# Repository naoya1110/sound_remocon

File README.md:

# sound_remocon

このリポジトリは、サウンドリモコンの開発データ（KiCadファイル等）をまとめたものです。

## ディレクトリ構成

- **v2/**  
  バージョン2
  - **kicad/**  
    v2用のKiCadプロジェクトファイル
    - `sound_remocon_v2/`：v2用KiCadプロジェクト・Gerberファイル
    - `plot_v2_20250704/`：v2 PCB製造用Gerberファイル
  - **ltspice/**  
    LTspiceシミュレーションファイル
    - `mixer_circuit_simulation.asc`：ミキサー回路シミュレーション
  - **pico_codes/**  
    - `pico_codes\sound_remocon_v2\sound_remocon_v2.ino` ラズパイPico用ファームウェア・コード

- **v1/**  
  バージョン1
  - **kicad/**  
    KiCadプロジェクトファイル、ネットリスト、シンボルライブラリ、フットプリント、Gerberファイルなど。

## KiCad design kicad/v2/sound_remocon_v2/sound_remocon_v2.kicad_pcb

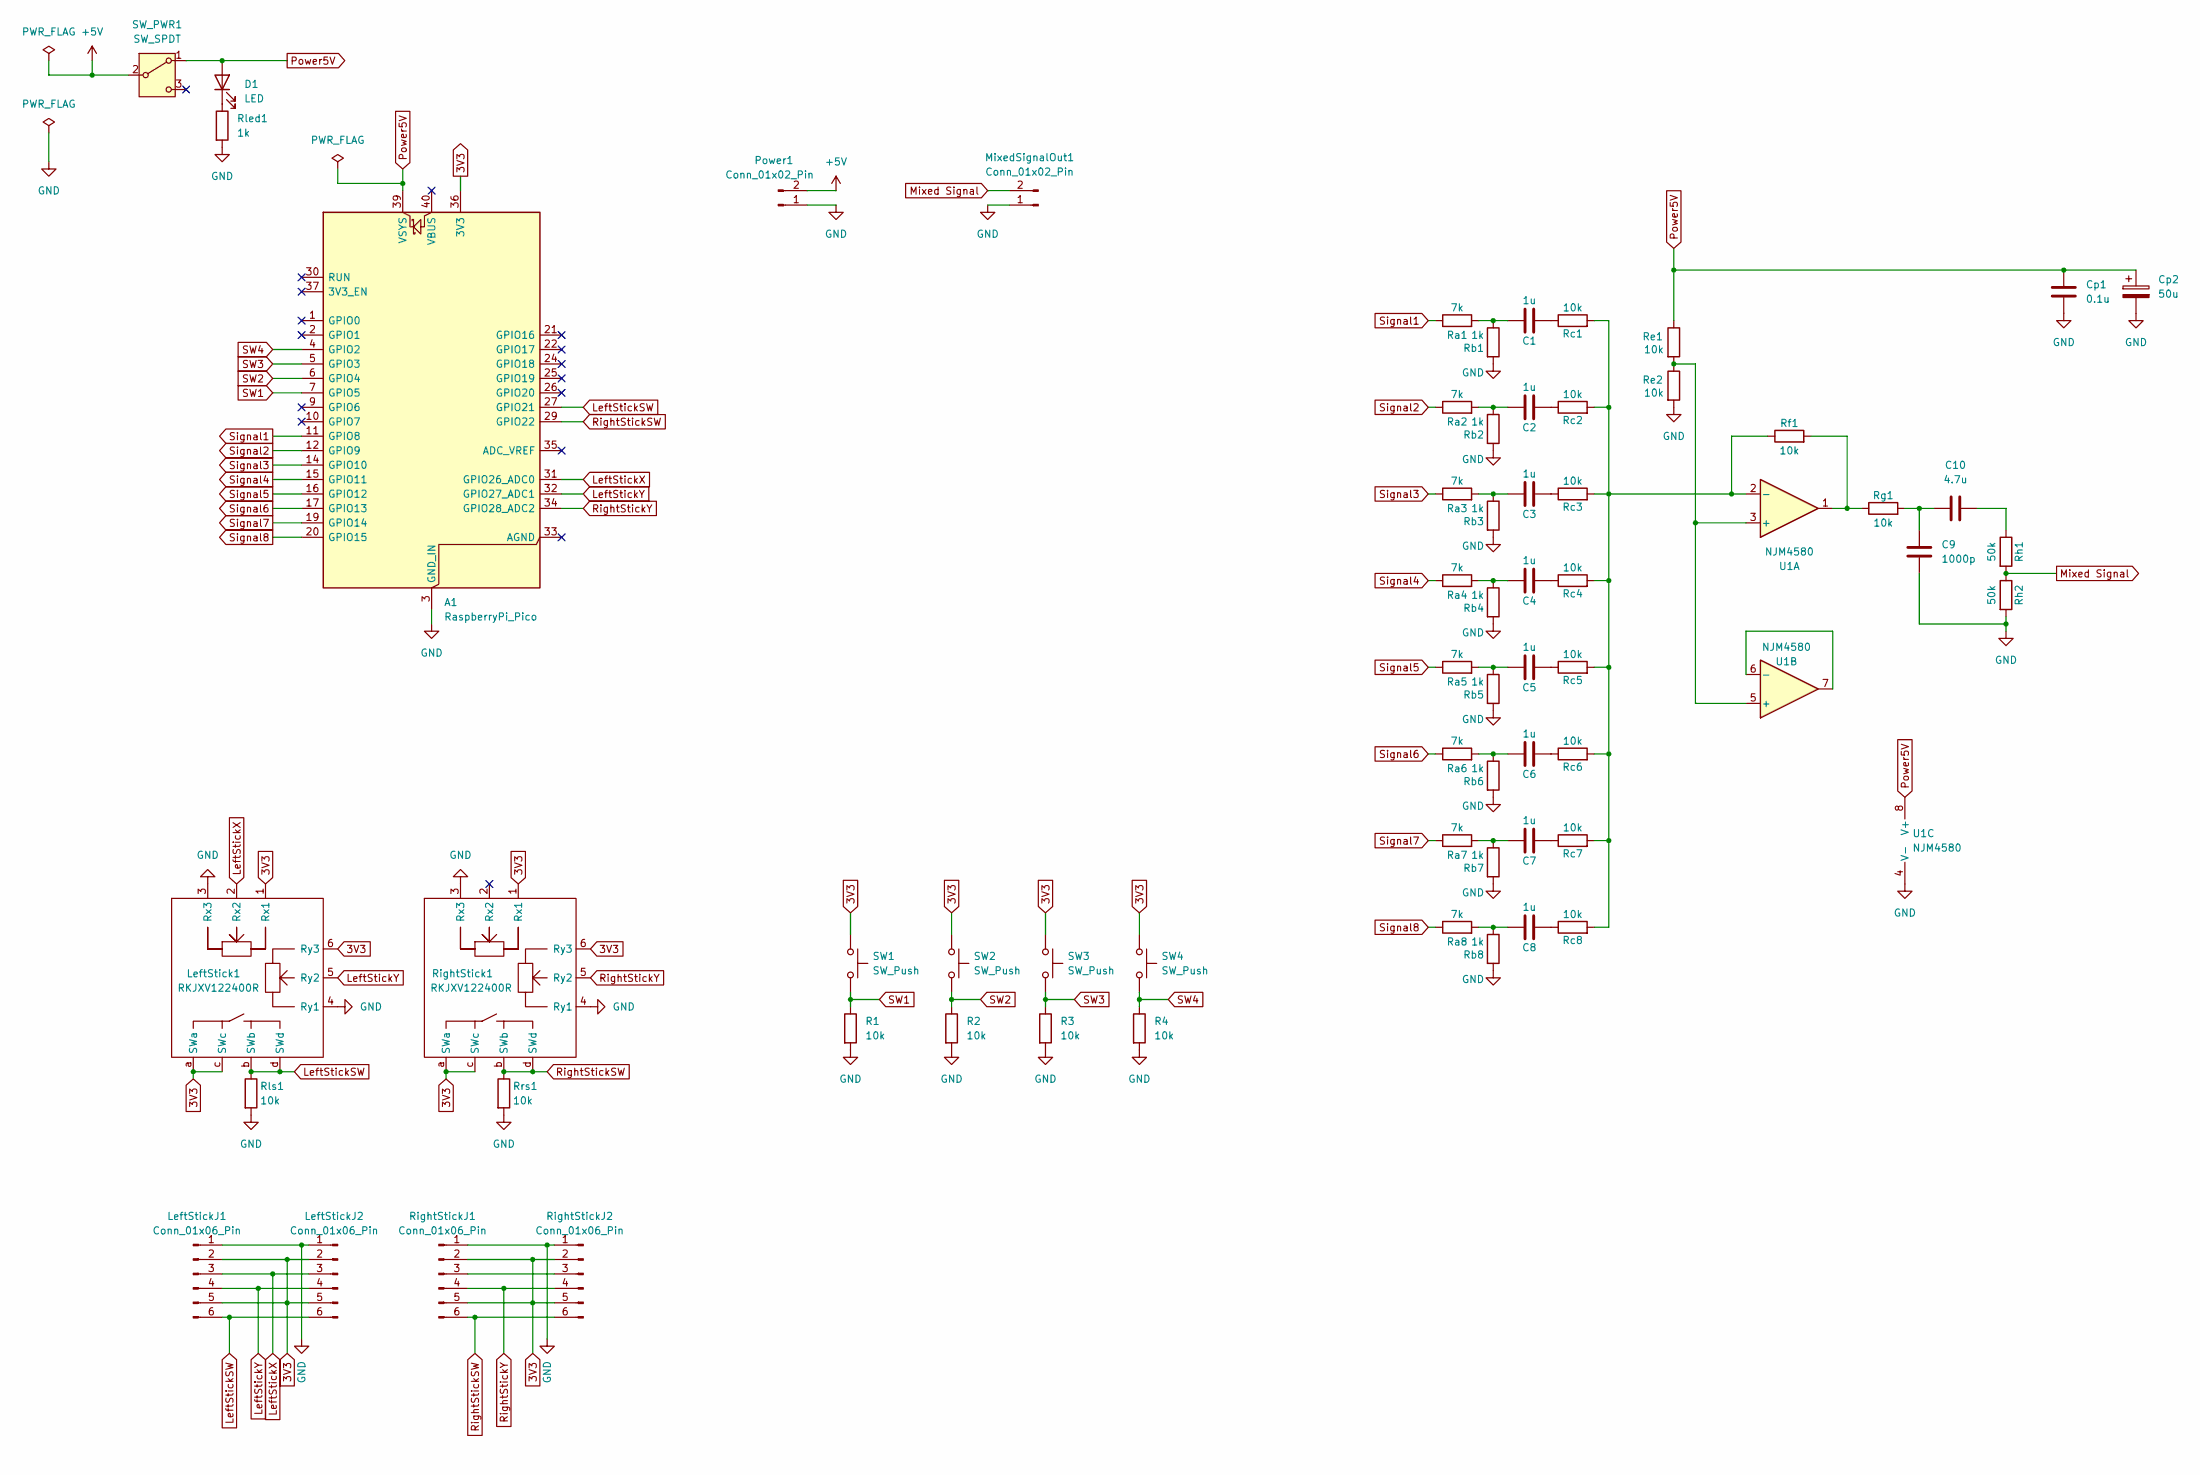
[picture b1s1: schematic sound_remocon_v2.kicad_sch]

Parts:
A1: RaspberryPi_Pico; RaspberryPi_Pico_Common_Unspecified
C1, C2, C3, C4, C5, C6, C7, C8: 1u; C_Disc_D5.1mm_W3.2mm_P5.00mm
C9: 1000p; C_Disc_D5.1mm_W3.2mm_P5.00mm
C10: 4.7u; C_Disc_D5.1mm_W3.2mm_P5.00mm
Cp1: 0.1u; C_Disc_D5.1mm_W3.2mm_P5.00mm
Cp2: 50u; CP_Radial_D8.0mm_P5.00mm
D1: LED; LED_D3.0mm
LeftStick1: RKJXV122400R
LeftStickJ1, LeftStickJ2: Conn_01x06_Pin; PinHeader_1x06_P2.54mm_Vertical
MixedSignalOut1: Conn_01x02_Pin; TerminalBlock_bornier-2_P5.08mm
Power1: Conn_01x02_Pin; TerminalBlock_bornier-2_P5.08mm
R1, R2, R3, R4: 10k; R_Axial_DIN0207_L6.3mm_D2.5mm_P2.54mm_Vertical
Ra1, Ra2, Ra3, Ra4, Ra5, Ra6, Ra7, Ra8: 7k; R_Axial_DIN0207_L6.3mm_D2.5mm_P2.54mm_Vertical
Rb1, Rb2, Rb3, Rb4, Rb5, Rb6, Rb7, Rb8: 1k; R_Axial_DIN0207_L6.3mm_D2.5mm_P2.54mm_Vertical
Rc1, Rc2, Rc3, Rc4, Rc5, Rc6, Rc7, Rc8: 10k; R_Axial_DIN0207_L6.3mm_D2.5mm_P2.54mm_Vertical
Re1, Re2: 10k; R_Axial_DIN0207_L6.3mm_D2.5mm_P2.54mm_Vertical
Rf1: 10k; R_Axial_DIN0207_L6.3mm_D2.5mm_P2.54mm_Vertical
Rg1: 10k; R_Axial_DIN0207_L6.3mm_D2.5mm_P2.54mm_Vertical
Rh1, Rh2: 50k; R_Axial_DIN0207_L6.3mm_D2.5mm_P2.54mm_Vertical
RightStick1: RKJXV122400R
RightStickJ1, RightStickJ2: Conn_01x06_Pin; PinHeader_1x06_P2.54mm_Vertical
Rled1: 1k; R_Axial_DIN0207_L6.3mm_D2.5mm_P2.54mm_Vertical
Rls1: 10k; R_Axial_DIN0207_L6.3mm_D2.5mm_P2.54mm_Vertical
Rrs1: 10k; R_Axial_DIN0207_L6.3mm_D2.5mm_P2.54mm_Vertical
SW1, SW2, SW3, SW4: SW_Push; SW_PUSH_6mm_H7.3mm
SW_PWR1: SW_SPDT; PinHeader_1x03_P2.54mm_Vertical
U1: NJM4580; DIP-8_W7.62mm_Socket

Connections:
3V3: A1.36 (3V3), LeftStick1.1 (Rx1), LeftStick1.6 (Ry3), LeftStick1.a (SWa), LeftStick1.c (SWc), LeftStickJ1.2, LeftStickJ1.5, LeftStickJ2.2, LeftStickJ2.5, RightStick1.1 (Rx1), RightStick1.6 (Ry3), RightStick1.a (SWa), RightStick1.c (SWc), RightStickJ1.2, RightStickJ1.5, RightStickJ2.2, RightStickJ2.5, SW1.1, SW2.1, SW3.1, SW4.1
+5V: Power1.2, SW_PWR1.2 (B)
GND: A1.3 (GND_IN), A1.8 (GND), A1.13 (GND), A1.18 (GND), A1.23 (GND), A1.28 (GND), A1.38 (GND), C9.2, Cp1.2, Cp2.2, LeftStick1.3 (Rx3), LeftStick1.4 (Ry1), LeftStickJ1.1, LeftStickJ2.1, MixedSignalOut1.1, Power1.1, R1.2, R2.2, R3.2, R4.2, Rb1.2, Rb2.2, Rb3.2, Rb4.2, Rb5.2, Rb6.2, Rb7.2, Rb8.2, Re2.2, Rh2.2, RightStick1.3 (Rx3), RightStick1.4 (Ry1), RightStickJ1.1, RightStickJ2.1, Rled1.2, Rls1.2, Rrs1.2, U1.4 (V-)
LeftStickSW: A1.27 (GPIO21), LeftStick1.b (SWb), LeftStick1.d (SWd), LeftStickJ1.6, LeftStickJ2.6, Rls1.1
LeftStickX: A1.31 (GPIO26_ADC0), LeftStick1.2 (Rx2), LeftStickJ1.3, LeftStickJ2.3
LeftStickY: A1.32 (GPIO27_ADC1), LeftStick1.5 (Ry2), LeftStickJ1.4, LeftStickJ2.4
Mixed Signal: MixedSignalOut1.2, Rh1.2, Rh2.1
unnamed: C1.1, Ra1.2, Rb1.1
unnamed: C1.2, Rc1.1
unnamed: C2.1, Ra2.2, Rb2.1
unnamed: C2.2, Rc2.1
unnamed: C3.1, Ra3.2, Rb3.1
unnamed: C3.2, Rc3.1
unnamed: C4.1, Ra4.2, Rb4.1
unnamed: C4.2, Rc4.1
unnamed: C5.1, Ra5.2, Rb5.1
unnamed: C5.2, Rc5.1
unnamed: C6.1, Ra6.2, Rb6.1
unnamed: C6.2, Rc6.1
unnamed: C7.1, Ra7.2, Rb7.1
unnamed: C7.2, Rc7.1
unnamed: C8.1, Ra8.2, Rb8.1
unnamed: C8.2, Rc8.1
unnamed: C9.1, C10.1, Rg1.2
unnamed: C10.2, Rh1.1
unnamed: D1.1 (K), Rled1.1
unnamed: Rf1.2, Rg1.1, U1.1
unnamed: RightStickJ1.3, RightStickJ2.3
unnamed: Re1.2, Re2.1, U1.3 (+), U1.5 (+)
unnamed: Rc1.2, Rc2.2, Rc3.2, Rc4.2, Rc5.2, Rc6.2, Rc7.2, Rc8.2, Rf1.1, U1.2 (-)
unnamed: U1.6 (-), U1.7
Power5V: A1.39 (VSYS), Cp1.1, Cp2.1, D1.2 (A), Re1.1, SW_PWR1.1 (A), U1.8 (V+)
RightStickSW: A1.29 (GPIO22), RightStick1.b (SWb), RightStick1.d (SWd), RightStickJ1.6, RightStickJ2.6, Rrs1.1
RightStickY: A1.34 (GPIO28_ADC2), RightStick1.5 (Ry2), RightStickJ1.4, RightStickJ2.4
SW1: A1.7 (GPIO5), R1.1, SW1.2
SW2: A1.6 (GPIO4), R2.1, SW2.2
SW3: A1.5 (GPIO3), R3.1, SW3.2
SW4: A1.4 (GPIO2), R4.1, SW4.2
Signal1: A1.11 (GPIO8), Ra1.1
Signal2: A1.12 (GPIO9), Ra2.1
Signal3: A1.14 (GPIO10), Ra3.1
Signal4: A1.15 (GPIO11), Ra4.1
Signal5: A1.16 (GPIO12), Ra5.1
Signal6: A1.17 (GPIO13), Ra6.1
Signal7: A1.19 (GPIO14), Ra7.1
Signal8: A1.20 (GPIO15), Ra8.1

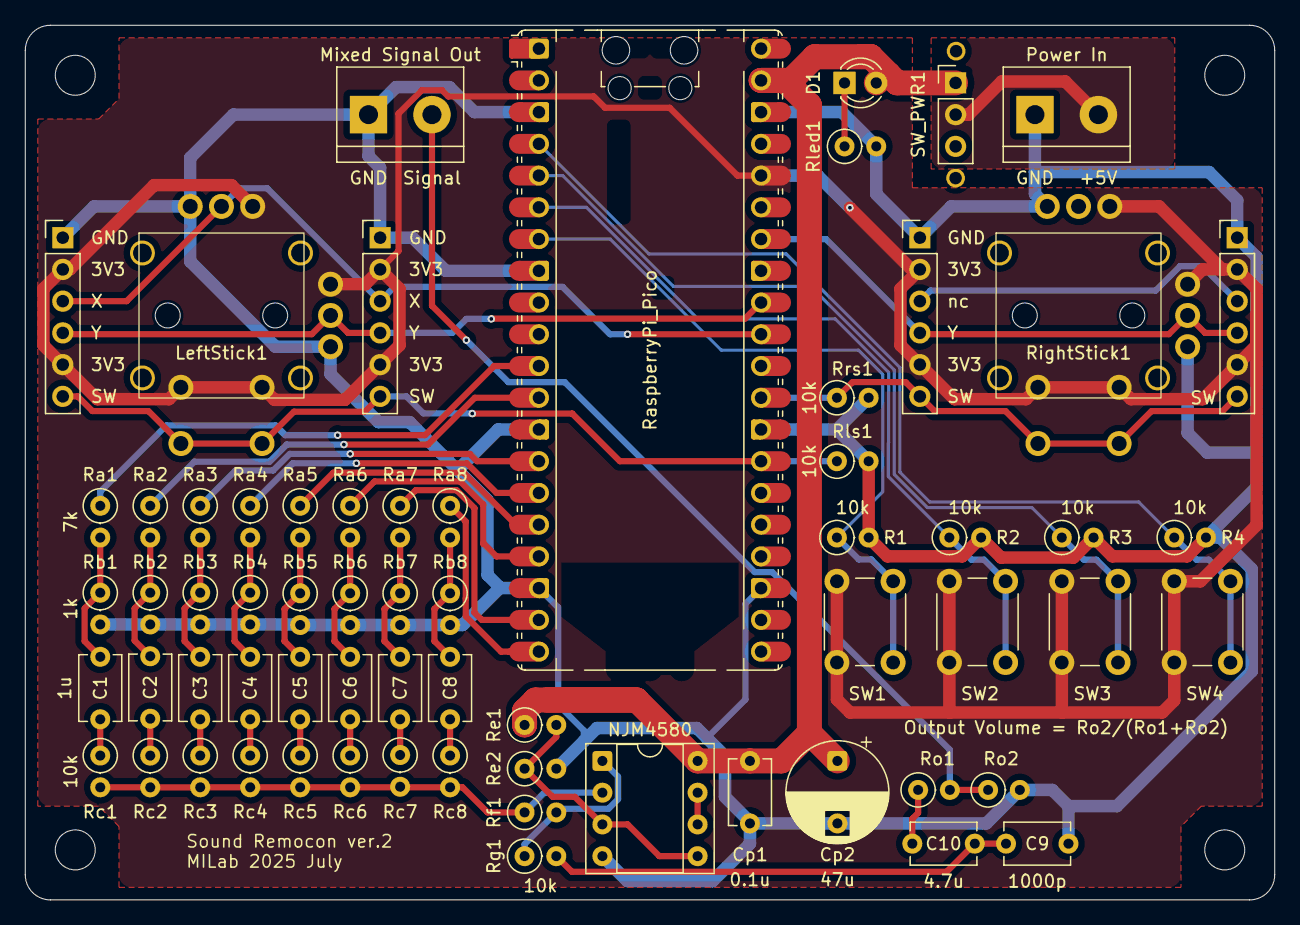
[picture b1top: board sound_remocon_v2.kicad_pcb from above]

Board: 2 copper layers, 100.0 x 70.0 mm, 65 parts (0 on the bottom side), 46 nets.

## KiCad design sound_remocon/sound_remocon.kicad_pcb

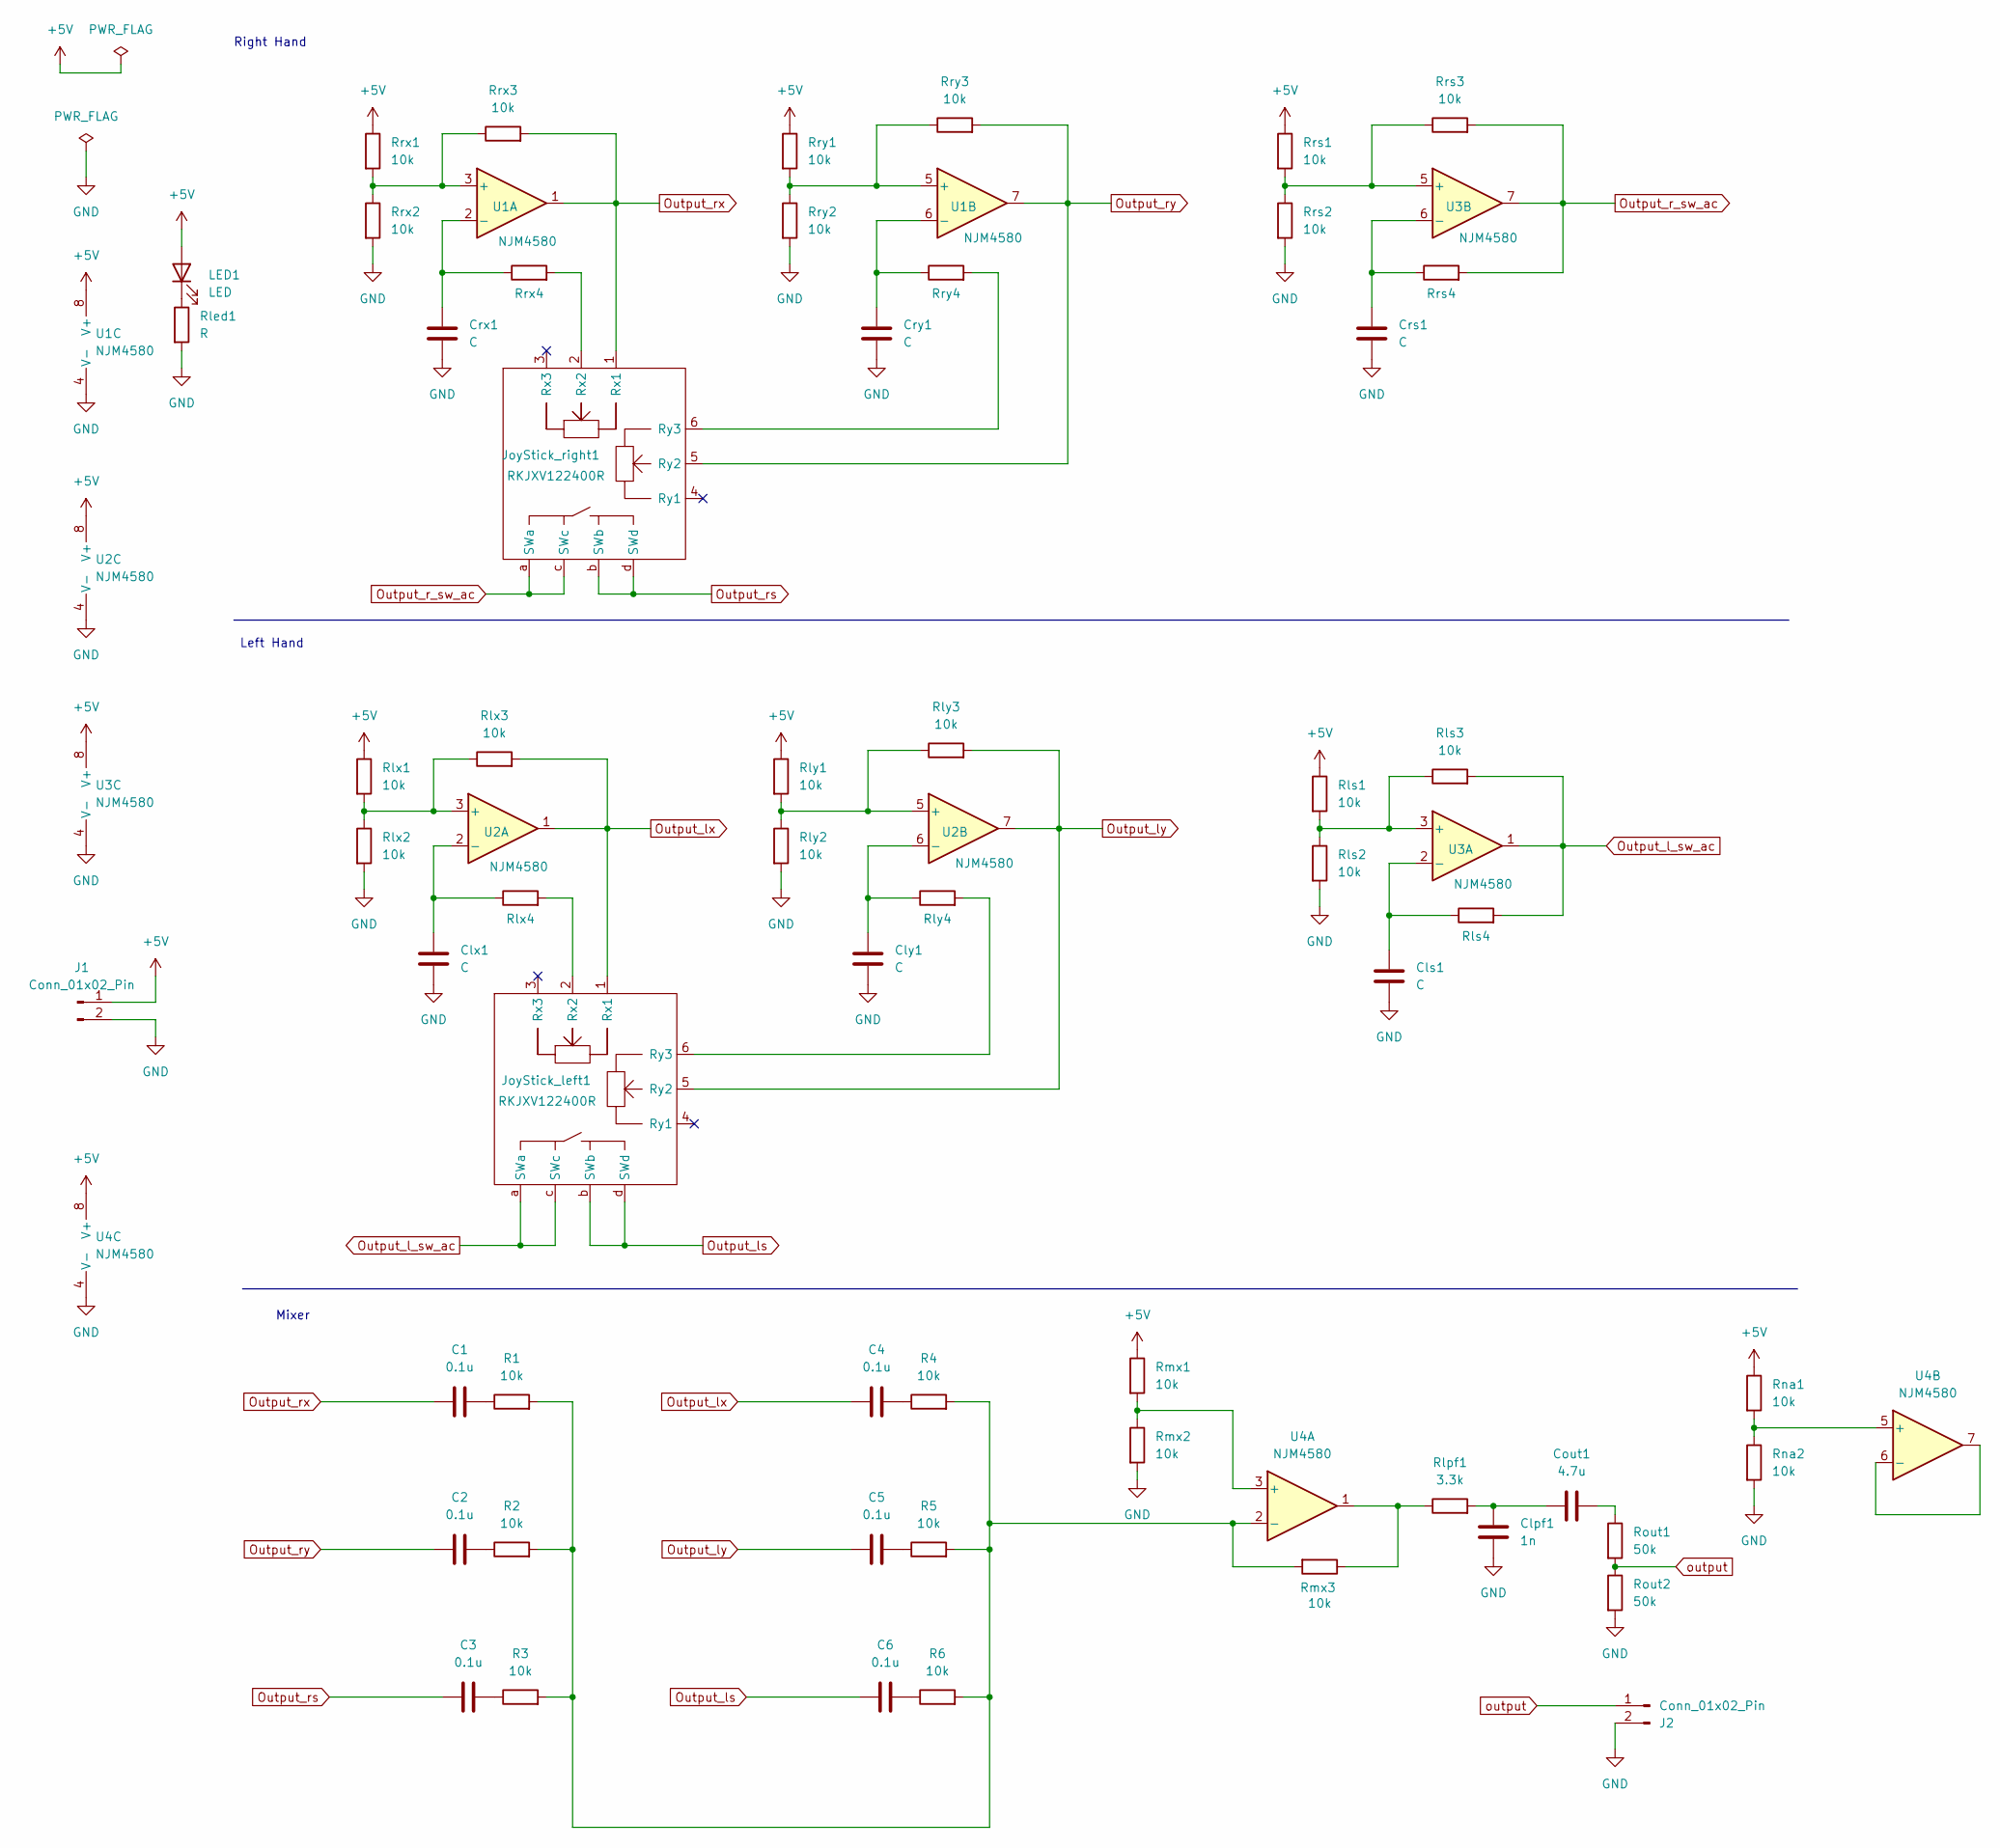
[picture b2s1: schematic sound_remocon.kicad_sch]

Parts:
C1, C2, C3, C4, C5, C6: 0.1u; C_Disc_D3.8mm_W2.6mm_P2.50mm
Clpf1: 1n; C_Disc_D3.8mm_W2.6mm_P2.50mm
Cls1: C; C_Disc_D3.8mm_W2.6mm_P2.50mm
Clx1: C; C_Disc_D3.8mm_W2.6mm_P2.50mm
Cly1: C; C_Disc_D3.8mm_W2.6mm_P2.50mm
Cout1: 4.7u; C_Disc_D4.7mm_W2.5mm_P5.00mm
Crs1: C; C_Disc_D3.8mm_W2.6mm_P2.50mm
Crx1: C; C_Disc_D3.8mm_W2.6mm_P2.50mm
Cry1: C; C_Disc_D3.8mm_W2.6mm_P2.50mm
J1, J2: Conn_01x02_Pin; TerminalBlock_bornier-2_P5.08mm
JoyStick_left1: RKJXV122400R
JoyStick_right1: RKJXV122400R
LED1: LED; LED_D3.0mm
R1, R2, R3, R4, R5, R6: 10k; R_Axial_DIN0207_L6.3mm_D2.5mm_P7.62mm_Horizontal
Rled1: R; R_Axial_DIN0207_L6.3mm_D2.5mm_P7.62mm_Horizontal
Rlpf1: 3.3k; R_Axial_DIN0207_L6.3mm_D2.5mm_P7.62mm_Horizontal
Rls1, Rls2, Rls3: 10k; R_Axial_DIN0207_L6.3mm_D2.5mm_P7.62mm_Horizontal
Rls4: R_Axial_DIN0207_L6.3mm_D2.5mm_P7.62mm_Horizontal
Rlx1, Rlx2, Rlx3: 10k; R_Axial_DIN0207_L6.3mm_D2.5mm_P7.62mm_Horizontal
Rlx4: R_Axial_DIN0207_L6.3mm_D2.5mm_P7.62mm_Horizontal
Rly1, Rly2, Rly3: 10k; R_Axial_DIN0207_L6.3mm_D2.5mm_P7.62mm_Horizontal
Rly4: R_Axial_DIN0207_L6.3mm_D2.5mm_P7.62mm_Horizontal
Rmx1, Rmx2, Rmx3: 10k; R_Axial_DIN0207_L6.3mm_D2.5mm_P7.62mm_Horizontal
Rna1, Rna2: 10k; R_Axial_DIN0207_L6.3mm_D2.5mm_P7.62mm_Horizontal
Rout1, Rout2: 50k; R_Axial_DIN0207_L6.3mm_D2.5mm_P7.62mm_Horizontal
Rrs1, Rrs2, Rrs3: 10k; R_Axial_DIN0207_L6.3mm_D2.5mm_P7.62mm_Horizontal
Rrs4: R_Axial_DIN0207_L6.3mm_D2.5mm_P7.62mm_Horizontal
Rrx1, Rrx2, Rrx3: 10k; R_Axial_DIN0207_L6.3mm_D2.5mm_P7.62mm_Horizontal
Rrx4: R_Axial_DIN0207_L6.3mm_D2.5mm_P7.62mm_Horizontal
Rry1, Rry2, Rry3: 10k; R_Axial_DIN0207_L6.3mm_D2.5mm_P7.62mm_Horizontal
Rry4: R_Axial_DIN0207_L6.3mm_D2.5mm_P7.62mm_Horizontal
U1, U2, U3, U4: NJM4580; DIP-8_W7.62mm

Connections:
+5V: J1.1, LED1.2 (A), Rls1.1, Rlx1.1, Rly1.1, Rmx1.1, Rna1.1, Rrs1.1, Rrx1.1, Rry1.1, U1.8 (V+), U2.8 (V+), U3.8 (V+), U4.8 (V+)
GND: Clpf1.2, Cls1.2, Clx1.2, Cly1.2, Crs1.2, Crx1.2, Cry1.2, J1.2, J2.2, Rled1.2, Rls2.2, Rlx2.2, Rly2.2, Rmx2.2, Rna2.2, Rout2.2, Rrs2.2, Rrx2.2, Rry2.2, U1.4 (V-), U2.4 (V-), U3.4 (V-), U4.4 (V-)
unnamed: C1.2, R1.1
unnamed: C2.2, R2.1
unnamed: C3.2, R3.1
unnamed: C4.2, R4.1
unnamed: C5.2, R5.1
unnamed: C6.2, R6.1
unnamed: Clpf1.1, Cout1.1, Rlpf1.2
unnamed: Cout1.2, Rout1.1
unnamed 10: JoyStick_left1.2 (Rx2), Rlx4.2; also elsewhere on the board
unnamed 11: JoyStick_left1.6 (Ry3), Rly4.2; also elsewhere on the board
unnamed 12: JoyStick_right1.2 (Rx2), Rrx4.2; also elsewhere on the board
unnamed 13: JoyStick_right1.6 (Ry3), Rry4.2; also elsewhere on the board
unnamed: LED1.1 (K), Rled1.1
unnamed: Rlpf1.1, Rmx3.1, U4.1
unnamed: Rrx1.2, Rrx2.1, Rrx3.1, U1.3 (+)
unnamed: Crx1.1, Rrx4.1, U1.2 (-)
unnamed: Rry1.2, Rry2.1, Rry3.1, U1.5 (+)
unnamed: Cry1.1, Rry4.1, U1.6 (-)
unnamed: Rlx1.2, Rlx2.1, Rlx3.1, U2.3 (+)
unnamed: Clx1.1, Rlx4.1, U2.2 (-)
unnamed: Rly1.2, Rly2.1, Rly3.1, U2.5 (+)
unnamed: Cly1.1, Rly4.1, U2.6 (-)
unnamed: Rls1.2, Rls2.1, Rls3.1, U3.3 (+)
unnamed: Cls1.1, Rls4.1, U3.2 (-)
unnamed: Rrs1.2, Rrs2.1, Rrs3.1, U3.5 (+)
unnamed: Crs1.1, Rrs4.1, U3.6 (-)
unnamed: Rmx1.2, Rmx2.1, U4.3 (+)
unnamed: R1.2, R2.2, R3.2, R4.2, R5.2, R6.2, Rmx3.2, U4.2 (-)
unnamed: Rna1.2, Rna2.1, U4.5 (+)
unnamed: U4.6 (-), U4.7
Output_l_sw_ac: JoyStick_left1.a (SWa), JoyStick_left1.c (SWc), Rls3.2, Rls4.2, U3.1; also elsewhere on the board
Output_ls: C6.1, JoyStick_left1.b (SWb), JoyStick_left1.d (SWd); also elsewhere on the board
Output_lx: C4.1, JoyStick_left1.1 (Rx1), Rlx3.2, U2.1; also elsewhere on the board
Output_ly: C5.1, JoyStick_left1.5 (Ry2), Rly3.2, U2.7; also elsewhere on the board
Output_r_sw_ac: JoyStick_right1.a (SWa), JoyStick_right1.c (SWc), Rrs3.2, Rrs4.2, U3.7; also elsewhere on the board
Output_rs: C3.1, JoyStick_right1.b (SWb), JoyStick_right1.d (SWd); also elsewhere on the board
Output_rx: C1.1, JoyStick_right1.1 (Rx1), Rrx3.2, U1.1; also elsewhere on the board
Output_ry: C2.1, JoyStick_right1.5 (Ry2), Rry3.2, U1.7; also elsewhere on the board
output: J2.1, Rout1.2, Rout2.1

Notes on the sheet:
Mixer
Left Hand
Right Hand

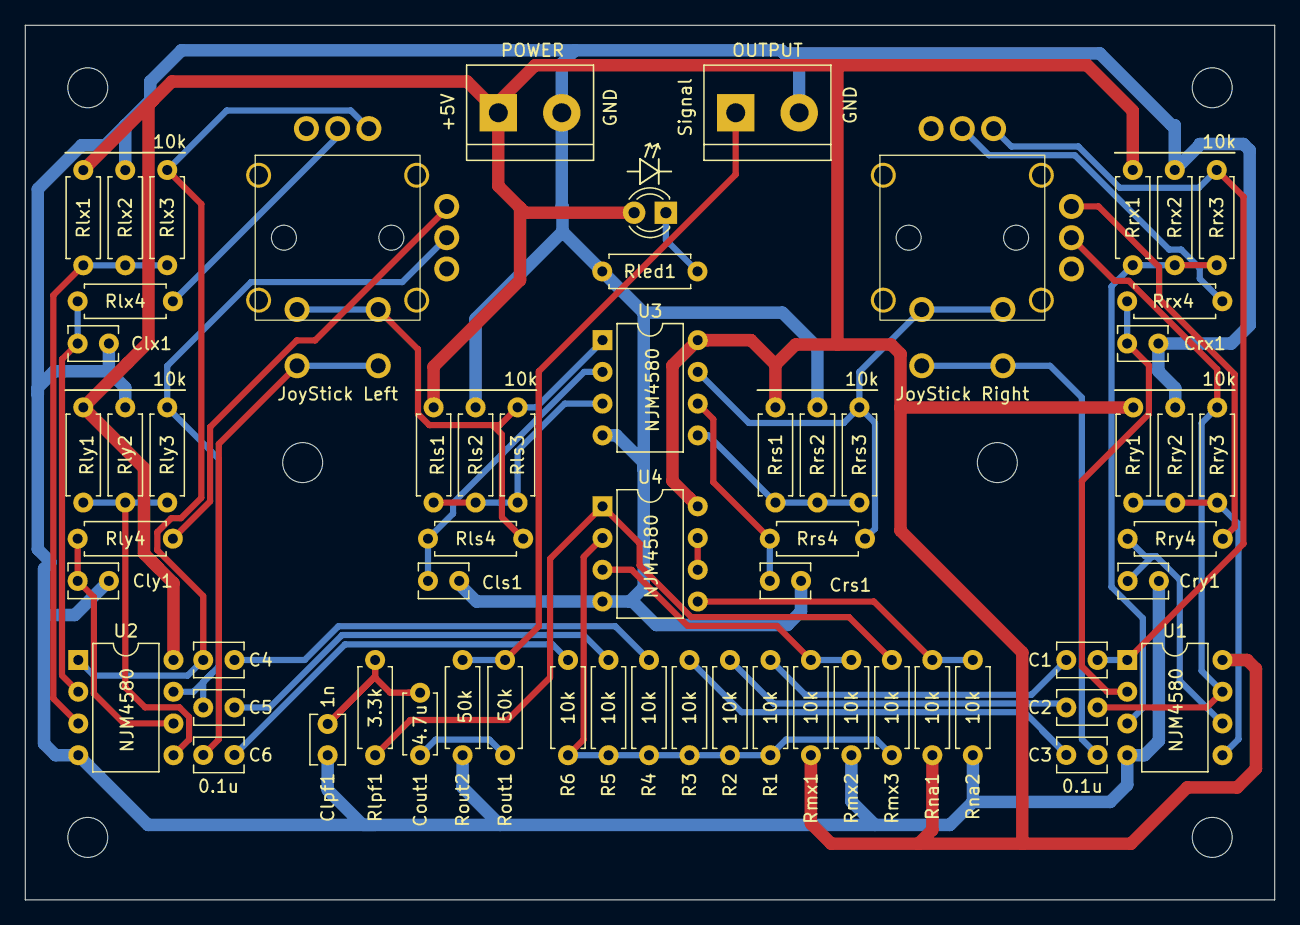
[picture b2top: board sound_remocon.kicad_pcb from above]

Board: 2 copper layers, 100.0 x 70.0 mm, 62 parts (0 on the bottom side), 41 nets.

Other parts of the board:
JoyStick Left: RKJXV122400R
JoyStick Right: RKJXV122400R

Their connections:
unnamed 10: JoyStick Left.2 (Rx2); also elsewhere on the board
unnamed 11: JoyStick Left.6 (Ry3); also elsewhere on the board
unnamed 12: JoyStick Right.2 (Rx2); also elsewhere on the board
unnamed 13: JoyStick Right.6 (Ry3); also elsewhere on the board
Output_l_sw_ac: JoyStick Left.a (SWa), JoyStick Left.c (SWc); also elsewhere on the board
Output_ls: JoyStick Left.b (SWb), JoyStick Left.d (SWd); also elsewhere on the board
Output_lx: JoyStick Left.1 (Rx1); also elsewhere on the board
Output_ly: JoyStick Left.5 (Ry2); also elsewhere on the board
Output_r_sw_ac: JoyStick Right.a (SWa), JoyStick Right.c (SWc); also elsewhere on the board
Output_rs: JoyStick Right.b (SWb), JoyStick Right.d (SWd); also elsewhere on the board
Output_rx: JoyStick Right.1 (Rx1); also elsewhere on the board
Output_ry: JoyStick Right.5 (Ry2); also elsewhere on the board

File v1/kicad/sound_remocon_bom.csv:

"Reference","Value","Datasheet","Footprint","Qty","DNP"
"C1,C2,C3,C4,C5,C6","0.1u","~","Capacitor_THT:C_Disc_D3.8mm_W2.6mm_P2.50mm","6",""
"Clpf1","1n","~","Capacitor_THT:C_Disc_D3.8mm_W2.6mm_P2.50mm","1",""
"Cls1,Clx1,Cly1,Crs1,Crx1,Cry1","C","~","Capacitor_THT:C_Disc_D3.8mm_W2.6mm_P2.50mm","6",""
"Cout1","4.7u","~","Capacitor_THT:C_Disc_D4.7mm_W2.5mm_P5.00mm","1",""
"J1,J2","Conn_01x02_Pin","~","TerminalBlock:TerminalBlock_bornier-2_P5.08mm","2",""
"JoyStick_left1,JoyStick_right1","RKJXV122400R","","myjoystick:RKJXV122400R","2",""
"LED1","LED","~","LED_THT:LED_D3.0mm","1",""
"R1,R2,R3,R4,R5,R6,Rls1,Rls2,Rls3,Rlx1,Rlx2,Rlx3,Rly1,Rly2,Rly3,Rmx1,Rmx2,Rmx3,Rna1,Rna2,Rrs1,Rrs2,Rrs3,Rrx1,Rrx2,Rrx3,Rry1,Rry2,Rry3","10k","~","Resistor_THT:R_Axial_DIN0207_L6.3mm_D2.5mm_P7.62mm_Horizontal","29",""
"Rled1","R","~","Resistor_THT:R_Axial_DIN0207_L6.3mm_D2.5mm_P7.62mm_Horizontal","1",""
"Rlpf1","3.3k","~","Resistor_THT:R_Axial_DIN0207_L6.3mm_D2.5mm_P7.62mm_Horizontal","1",""
"Rls4,Rlx4,Rly4,Rrs4,Rrx4,Rry4","~","~","Resistor_THT:R_Axial_DIN0207_L6.3mm_D2.5mm_P7.62mm_Horizontal","6",""
"Rout1,Rout2","50k","~","Resistor_THT:R_Axial_DIN0207_L6.3mm_D2.5mm_P7.62mm_Horizontal","2",""
"U1,U2,U3,U4","NJM4580","http://www.njr.com/semicon/PDF/NJM4580_E.pdf","Package_DIP:DIP-8_W7.62mm","4",""

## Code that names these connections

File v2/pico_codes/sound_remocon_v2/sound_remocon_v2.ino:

// Raspberry Pi Pico 2 Pin Configuration
//
// INPUT                          |   OUTPUT
// -------------------------------|--------------------------------------
// SW1 ----------------> GPIO5 ---|-- GPIO8 ------> Signal1 ----- 800Hz
// SW2 ----------------> GPIO4 ---|-- GPIO9 ------> Signal2 ----- 850Hz
// SW3 ----------------> GPIO3 ---|-- GPIO10 -----> Signal3 ----- 900Hz
// SW4 ----------------> GPIO2 ---|-- GPIO11 -----> Signal4 ----- 950Hz
// LEFT STICK SW ------> GPIO21 --|-- GPIO12 -----> Signal5 ----- 1000Hz
// RIGHT STICK SW -----> GPIO22 --|-- GPIO13 -----> Signal6 ----- 1050Hz
// LEFT STICK X -------> ADC0 ----|-- None -------> None
// LEFT STICK Y -------> ADC1 ----|-- GPIO14 -----> Signal7 ----- 510-550-590Hz
// RIGHT STICK Y ------> ADC2 ----|-- GPIO15 -----> Signal8 ----- 660-700-740Hz
// -------------------------------|--------------------------------------



#include <Arduino.h>

#define TONE_USE_INT
#define TONE_PITCH 440
#include <TonePitch.h>

// ボタンスイッチ
#define PIN_SW1 5
#define PIN_SW2 4
#define PIN_SW3 3
#define PIN_SW4 2

// スティックのボタンスイッチ
#define PIN_L_ST_SW 21
#define PIN_R_ST_SW 22

// スティックのXY
#define PIN_L_ST_X A0
#define PIN_L_ST_Y A1
#define PIN_R_ST_Y A2

// 矩形波信号出力
#define PIN_SIGNAL1 8
#define PIN_SIGNAL2 9
#define PIN_SIGNAL3 10
#define PIN_SIGNAL4 11
#define PIN_SIGNAL5 12
#define PIN_SIGNAL6 13
#define PIN_SIGNAL7 14
#define PIN_SIGNAL8 15

// 信号の基本周波数
#define FREQ_SIGNAL1 800
#define FREQ_SIGNAL2 850
#define FREQ_SIGNAL3 900
#define FREQ_SIGNAL4 950
#define FREQ_SIGNAL5 1000
#define FREQ_SIGNAL6 1050
#define FREQ_SIGNAL7 550
#define FREQ_SIGNAL8 700

#define FREQ_STEP 10

int oldSw1State = 0;
int oldSw2State = 0;
int oldSw3State = 0;
int oldSw4State = 0;
int oldLeftStickSwState = 0;
int oldRightStickSwState = 0;
int oldMappedLeftStickXValue = 0;
int oldMappedLeftStickYValue = 0;
int oldMappedRightStickYValue = 0;

// スティックの値
int leftStickXValue = 0;
int leftStickYValue = 0;
int rightStickYValue = 0;


void setup() {
  Serial.begin(9600);
  
  // 入力ピン
  pinMode(PIN_SW1, INPUT);      // digital
  pinMode(PIN_SW2, INPUT);      // digital
  pinMode(PIN_SW3, INPUT);      // digital
  pinMode(PIN_SW4, INPUT);      // digital
  pinMode(PIN_L_ST_SW, INPUT);  // digital
  pinMode(PIN_R_ST_SW, INPUT);  // digital
  pinMode(PIN_L_ST_X, INPUT);   // analog
  pinMode(PIN_L_ST_Y, INPUT);   // analog
  pinMode(PIN_R_ST_Y, INPUT);   // analog

  // 出力ピン
  pinMode(LED_BUILTIN, OUTPUT); // ボード上のLED

  pinMode(PIN_SIGNAL1, OUTPUT);  // SW1
  pinMode(PIN_SIGNAL2, OUTPUT);  // SW2
  pinMode(PIN_SIGNAL3, OUTPUT);  // SW3
  pinMode(PIN_SIGNAL4, OUTPUT);  // SW4
  pinMode(PIN_SIGNAL5, OUTPUT);  // Left Stick SW
  pinMode(PIN_SIGNAL6, OUTPUT);  // Right Stick SW
  pinMode(PIN_SIGNAL7, OUTPUT);  // Left Stick X
  pinMode(PIN_SIGNAL8, OUTPUT);  // Left Stick Y

  tone(PIN_SIGNAL7, FREQ_SIGNAL7);
  tone(PIN_SIGNAL8, FREQ_SIGNAL8);
}

// スティックの味付け関数
int map_stick(int x) {
  int y;
  if (abs(x) < 75) {
    y = 0;
  } else {
    y = round(x/90);
    y = min(4, y);
    y = max(-4, y);
  }
  return y;
}

void loop() {

  Serial.println("Calibating.....");
  // スティックのキャリブレーション

  // スティックのニュートラル値
  int neutralLeftStickX = 0;
  int neutralLeftStickY = 0;
  int neutralRightStickY = 0;
  int nCalib = 30;

  for (int i=0; i<nCalib; i++) {
    digitalWrite(LED_BUILTIN, HIGH);
    neutralLeftStickX += analogRead(PIN_L_ST_X);
    neutralLeftStickY += analogRead(PIN_L_ST_Y);
    neutralRightStickY += analogRead(PIN_R_ST_Y);
    delay(100);
    digitalWrite(LED_BUILTIN, LOW);
    delay(50);
  }

  neutralLeftStickX /= nCalib;
  neutralLeftStickY /= nCalib;
  neutralRightStickY /= nCalib;
  
  Serial.println("Stick Neutral Values");
  Serial.print(neutralLeftStickX);
  Serial.print("\t");
  Serial.print(neutralLeftStickY);
  Serial.print("\t");
  Serial.println(neutralRightStickY);
  delay(2000);

  while(1) {
    digitalWrite(LED_BUILTIN, HIGH);

    // ボタンスイッチの値を読み取り
    int sw1State = digitalRead(PIN_SW1);
    int sw2State = digitalRead(PIN_SW2);
    int sw3State = digitalRead(PIN_SW3);
    int sw4State = digitalRead(PIN_SW4);
    int leftStickSwState = digitalRead(PIN_L_ST_SW);
    int rightStickSwState = digitalRead(PIN_R_ST_SW);

    // スティックの値の読み取り
    leftStickXValue = analogRead(PIN_L_ST_X);
    leftStickYValue = analogRead(PIN_L_ST_Y);
    rightStickYValue = analogRead(PIN_R_ST_Y);

    leftStickXValue -= neutralLeftStickX;
    leftStickYValue -= neutralLeftStickY;
    rightStickYValue -= neutralRightStickY;

    // スティックの値をマップ -4から+4にマップ
    int mappedLeftStickXValue = map_stick(leftStickXValue);
    int mappedLeftStickYValue = map_stick(leftStickYValue);
    int mappedRightStickYValue = map_stick(rightStickYValue);

    // SW1/Signal1の信号制御
    if (sw1State != oldSw1State) {
      if (sw1State == 1) {
        tone(PIN_SIGNAL1, FREQ_SIGNAL1);
      } else if (sw1State == 0) {
        noTone(PIN_SIGNAL1);
      }
    }

    // SW2/Signal2の信号制御
    if (sw2State != oldSw2State) {
      if (sw2State == 1) {
        tone(PIN_SIGNAL2, FREQ_SIGNAL2);
      } else if (sw2State == 0) {
        noTone(PIN_SIGNAL2);
      }
    }

    // SW3/Signal3の信号制御
    if (sw3State != oldSw3State) {
      if (sw3State == 1) {
        tone(PIN_SIGNAL3, FREQ_SIGNAL3);
      } else if (sw3State == 0) {
        noTone(PIN_SIGNAL3);
      }
    }

    // SW4/Signal4の信号制御
    if (sw4State != oldSw4State) {
      if (sw4State == 1) {
        tone(PIN_SIGNAL4, FREQ_SIGNAL4);
      } else if (sw4State == 0) {
        noTone(PIN_SIGNAL4);
      }
    }

    // LeftStickSW/Signal5の信号制御
    if (leftStickSwState != oldLeftStickSwState) {
      if (leftStickSwState == 1) {
        tone(PIN_SIGNAL5, FREQ_SIGNAL5);
      } else if (leftStickSwState == 0) {
        noTone(PIN_SIGNAL5);
      }
    }

    // RightStickSW/Signal6の信号制御
    if (rightStickSwState != oldRightStickSwState) {
      if (rightStickSwState == 1) {
        tone(PIN_SIGNAL6, FREQ_SIGNAL6);
      } else if (rightStickSwState == 0) {
        noTone(PIN_SIGNAL6);
      }
    }

    // // LeftStickXValue/Signal7の信号制御
    // if (mappedLeftStickXValue != oldMappedLeftStickXValue){
    //   int f = FREQ_SIGNAL7 + mappedLeftStickXValue * FREQ_STEP;
    //   tone(PIN_SIGNAL7, f);
    // }

    // LeftStickYValue/Signal7の信号制御
    if (mappedLeftStickYValue != oldMappedLeftStickYValue){
      int f = FREQ_SIGNAL7 + mappedLeftStickYValue * FREQ_STEP;
      tone(PIN_SIGNAL7, f);
    }

    // RightStickYValue/Signal8の信号制御
    if (mappedRightStickYValue != oldMappedRightStickYValue){
      int f = FREQ_SIGNAL8 + mappedRightStickYValue * FREQ_STEP;
      tone(PIN_SIGNAL8, f);
    }



    Serial.print(sw1State);
    Serial.print("\t");
    Serial.print(sw2State);
    Serial.print("\t");
    Serial.print(sw3State);
    Serial.print("\t");
    Serial.print(sw4State);
    Serial.print("\t");
    Serial.print(leftStickSwState);
    Serial.print("\t");
    Serial.print(rightStickSwState);
    Serial.print("\t");
    Serial.print(leftStickXValue);
    Serial.print("\t");
    Serial.print(mappedLeftStickXValue);
    Serial.print("\t");
    Serial.print(leftStickYValue);
    Serial.print("\t");
    Serial.print(mappedLeftStickYValue);
    Serial.print("\t");
    Serial.print(rightStickYValue);
    Serial.print("\t");
    Serial.println(mappedRightStickYValue);

    // 古いデータを保持
    oldSw1State = sw1State;
    oldSw2State = sw2State;
    oldSw3State = sw3State;
    oldSw4State = sw4State;

    oldLeftStickSwState = leftStickSwState;
    oldRightStickSwState = rightStickSwState;

    oldMappedLeftStickXValue = mappedLeftStickXValue;
    oldMappedLeftStickYValue = mappedLeftStickYValue;
    oldMappedRightStickYValue = mappedRightStickYValue;


    delay(10);  // wait for a second

  }

  


}
